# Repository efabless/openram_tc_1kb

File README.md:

# openram_tc_1kb Breakout Board & Documentation

------>>>> WORK IN PROGRESS <<<<-------

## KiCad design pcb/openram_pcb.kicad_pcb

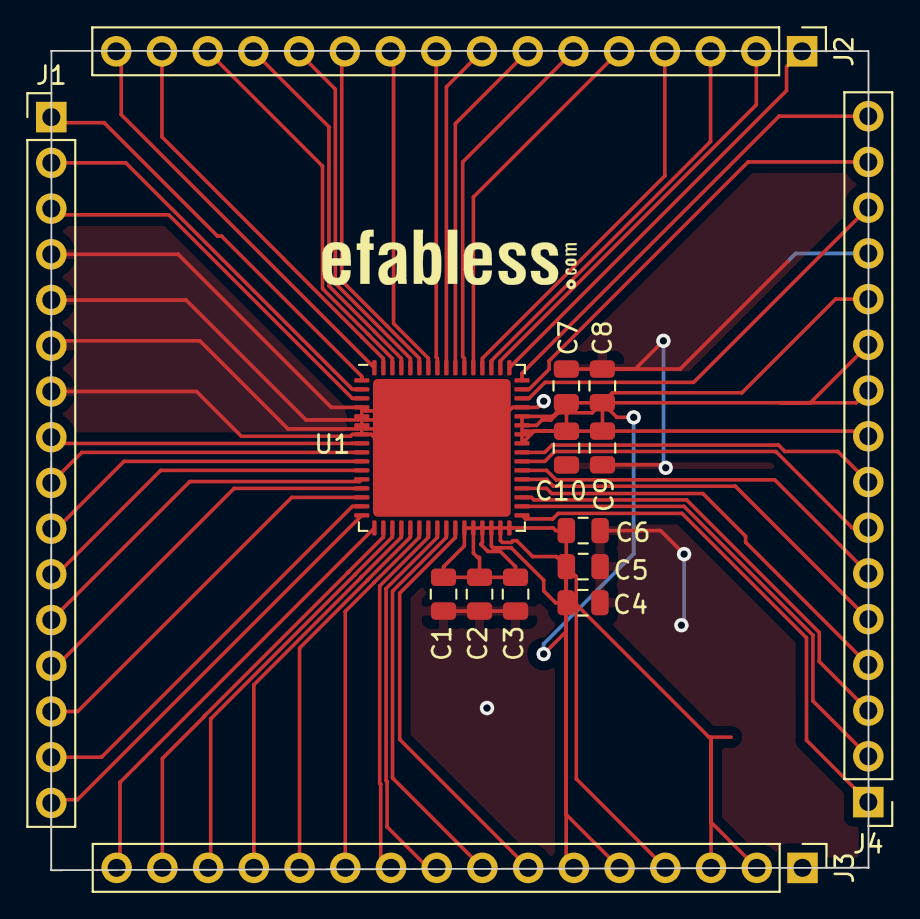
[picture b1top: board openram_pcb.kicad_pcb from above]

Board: 2 copper layers, 45.4 x 45.5 mm, 16 parts (0 on the bottom side), 51 nets.

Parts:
C1, C2, C3, C4, C5, C6, C7, C8, C9, C10: C; C_0805_2012Metric
J1, J2, J3, J4: Conn_01x16_Male; PinHeader_1x16_P2.54mm_Vertical
U1: openram_pkg_symbol; QFN-64-1EP_9x9mm_P0.5mm_EP7.65x7.65mm
U2: logo; logo_footprint

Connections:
+3V3: C1.1, C2.1, C3.1, C4.1, C5.1, C6.1, C7.1, C8.1, C9.1, C10.1, J3.1, J3.2, J3.3, J3.4, J3.5, J3.6, J4.9, J4.10, J4.11, J4.12, U1.27, U1.28, U1.29, U1.30, U1.31, U1.32, U1.41, U1.42, U1.43, U1.44
GND: C1.2, C2.2, C3.2, C4.2, C5.2, C6.2, C7.2, C8.2, C9.2, C10.2, J1.4, J1.5, J1.6, J1.7, J4.13, U1.4, U1.5, U1.6, U1.7, U1.45, U1.65
addr0[0]: J1.2, U1.2
addr0[1]: J1.10, U1.10
addr0[2]: J1.11, U1.11
addr0[3]: J1.12, U1.12
addr0[4]: J1.13, U1.13
addr0[5]: J1.14, U1.14
addr0[6]: J1.15, U1.15
addr0[7]: J1.16, U1.16
addr1[0]: J3.8, U1.25
addr1[1]: J4.2, U1.34
addr1[2]: J4.3, U1.35
addr1[3]: J4.4, U1.36
addr1[4]: J4.5, U1.37
addr1[5]: J4.6, U1.38
addr1[6]: J4.7, U1.39
addr1[7]: J4.8, U1.40
clk0: J1.3, U1.3
clk1: J3.7, U1.26
csb0: J1.8, U1.8
csb1: J4.1, U1.33
din0_0: J2.13, U1.61
din0_7: J2.10, U1.58
din0_8: J2.8, U1.56
din0_15: J2.7, U1.55
din0_16: J2.5, U1.53
din0_23: J2.3, U1.51
din0_24: J2.1, U1.49
din0_31: J4.15, U1.47
dout0_0: J2.12, U1.60
dout0_7: J2.11, U1.59
dout0_8: J2.9, U1.57
dout0_15: J2.6, U1.54
dout0_16: J2.4, U1.52
dout0_23: J2.2, U1.50
dout0_24: J4.16, U1.48
dout0_31: J4.14, U1.46
dout1_0: J3.9, U1.24
dout1_7: J3.15, U1.18
dout1_8: J3.16, U1.17
dout1_15: J3.10, U1.23
dout1_16: J3.11, U1.22
dout1_23: J3.12, U1.21
dout1_24: J3.13, U1.20
dout1_31: J3.14, U1.19
web0: J1.9, U1.9
wmask0[0]: J2.14, U1.62
wmask0[1]: J2.15, U1.63
wmask0[2]: J2.16, U1.64
wmask0[3]: J1.1, U1.1

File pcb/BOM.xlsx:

Part / Designator | MPN | Quantity | Seeed SKU
C1,C2,C3,C4,C5,C6,C7,C8,C9,C10 | CC0805KRX7R9BB104 | 10 | 302010165
U1 | openRAM | 1

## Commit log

2021-05-11 Publishing the pcb/package information for the openram_tc_1kb
